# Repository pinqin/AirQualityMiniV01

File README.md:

# AirQualityMiniV01

This repository contains the design files for a printed circuit board (PCB) featuring an ESP32-C3 microcontroller and a BME688 environmental sensor.
Included are schematics, PCB layout files, and the bill of materials (BOM).
Key Components (BOM excerpt)

U1: BME688 (environmental sensor)

U2: ESP32-C3 (WiFi/Bluetooth SoC)

U3: USB-C connector – DX07S016JA1R1500

U4: Antenna – ANT3216LL00R2400A

U5: Voltage regulator – TLV62568DBVR

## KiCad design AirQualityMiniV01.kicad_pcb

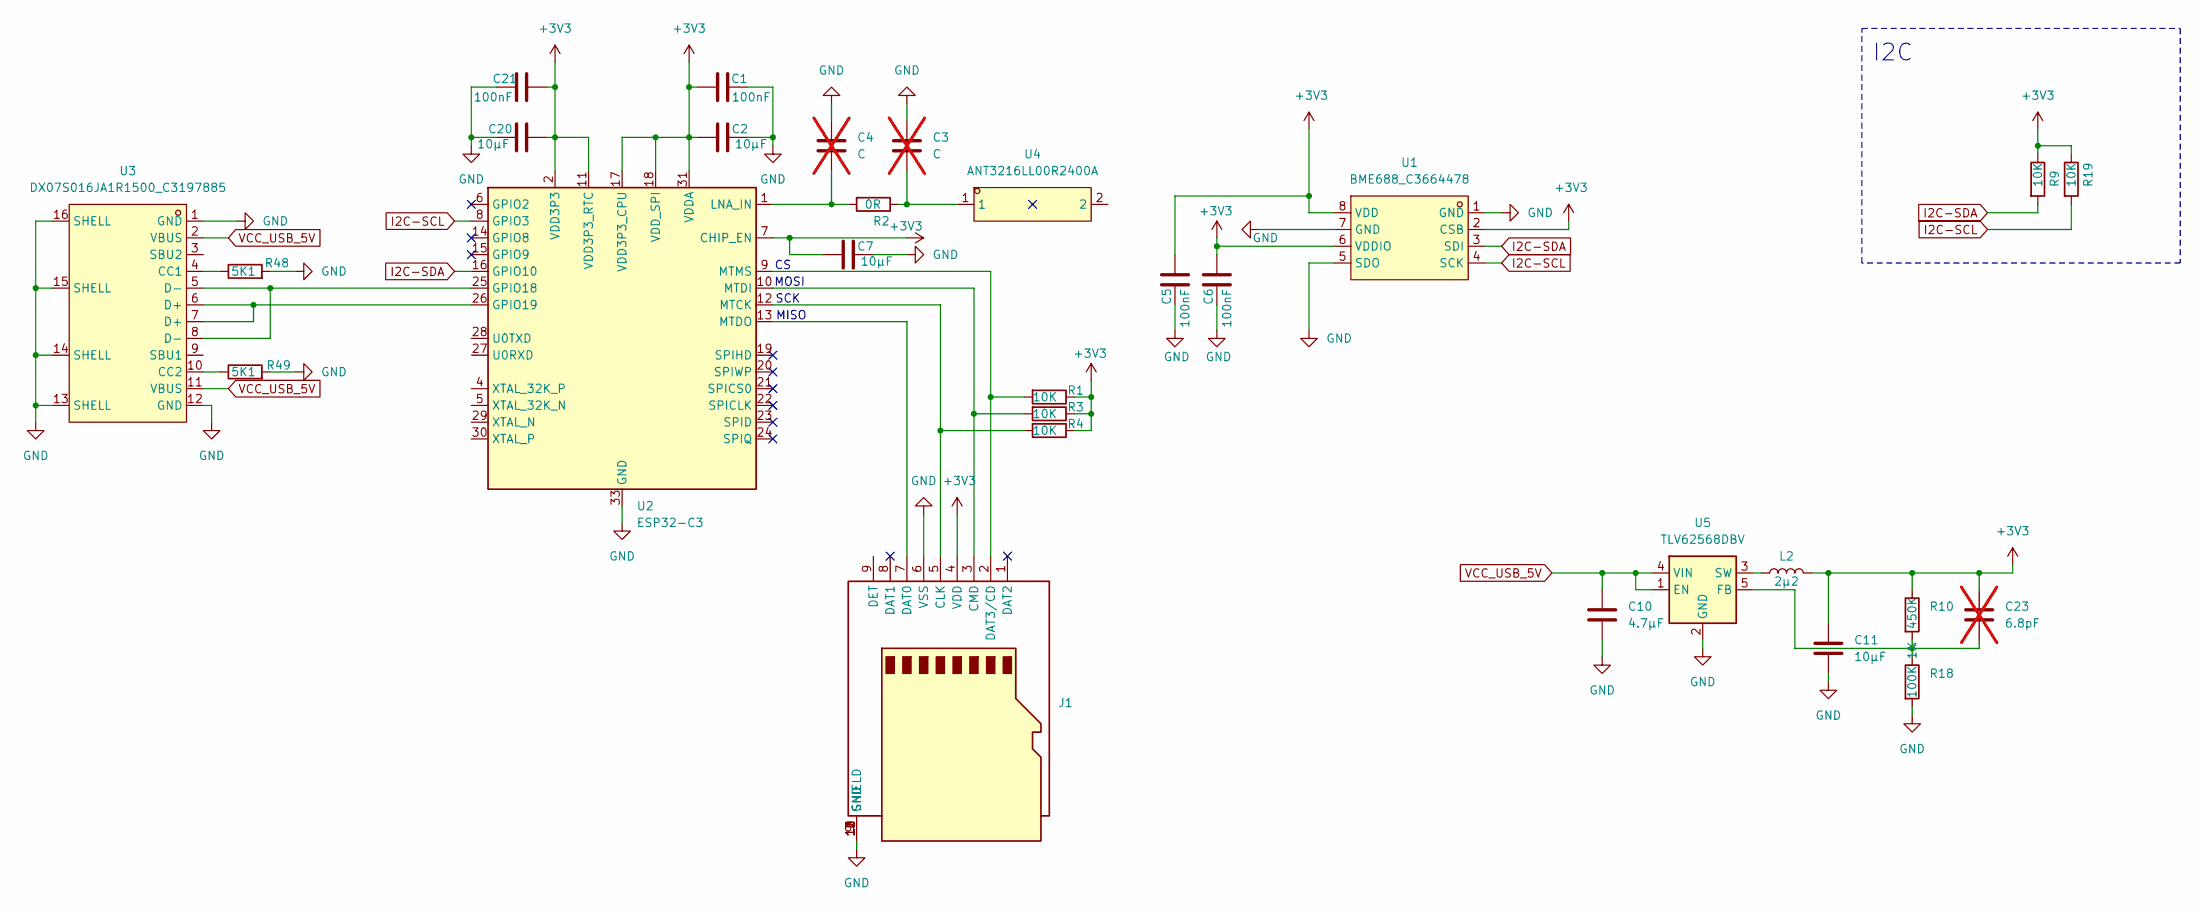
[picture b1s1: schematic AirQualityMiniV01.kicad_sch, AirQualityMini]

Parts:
C1, C5, C6, C21: 100nF; C_0603_1608Metric; MPN CC0603KRX7R9BB104; LCSC Partnumber C14663
C2, C7, C20: 10µF; C_0603_1608Metric; MPN GRM188R61A106KE69D; LCSC Partnumber C77044
C3, C4: C; C_0603_1608Metric; not fitted
C10: 4.7µF; C_0805_2012Metric; MPN GRM21BR71A475KA73L; LCSC Partnumber C86039
C11: 10µF; C_0805_2012Metric; MPN GRM21BR71A106KE51L; LCSC Partnumber C86038
C23: 6.8pF; C_0603_1608Metric; MPN CC0402CRNPO9BN6R8; LCSC Partnumber C189470; not fitted
J1: 1051620001; MPN 1051620001; LCSC Partnumber C3177046
L2: 2µ2; L_1008_2520Metric; MPN WIP252010P-2R2ML; LCSC C315713
R1, R3, R4, R9, R19: 10K; R_0603_1608Metric; MPN RC0603FR-0710KL; LCSC Partnumber C98220
R2: 0R; R_0603_1608Metric; MPN RC0603JR-070RL; LCSC Partnumber C95177
R10: 450K; R_0402_1005Metric; MPN FRC0402F4503TS; LCSC Partnumber C5159688
R18: 100K 1%; R_0603_1608Metric; MPN RC0603FR-07100KL; LCSC Partnumber C14675
R48, R49: 5K1; R_0603_1608Metric; MPN RC0603FR-075K1L; LCSC Partnumber C105580
U1: BME688_C3664478; LGA-8_L3.0-W3.0-P0.80_BME688; MPN BME688; LCSC Part C3664478
U2: ESP32-C3; QFN-32-1EP_5x5mm_P0.5mm_EP3.7x3.7mm; MPN ESP32-C3
U3: DX07S016JA1R1500_C3197885; USB-C-SMD_DX07S016JA1R1500; LCSC Part C3197885
U4: ANT3216LL00R2400A; ANT-SMD_L3.2-W1.6; MPN ANT3216LL00R2400A; LCSC Part C293767
U5: TLV62568DBV; SOT-23-5; MPN TLV62568DBVR; LCSC Partnumber C163219

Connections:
+3V3: C1.2, C2.2, C5.2, C6.2, C7.2, C11.1, C20.2, C21.2, C23.1, J1.4 (VDD), L2.2, R1.1, R3.1, R4.1, R9.1, R10.1, R19.1, U1.2 (CSB), U1.6 (VDDIO), U1.8 (VDD), U2.2 (VDD3P3), U2.3 (VDD3P3), U2.7 (CHIP_EN), U2.11 (VDD3P3_RTC), U2.17 (VDD3P3_CPU), U2.18 (VDD_SPI), U2.31 (VDDA), U2.32 (VDDA)
GND: C1.1, C2.1, C3.1, C4.1, C5.1, C6.1, C7.1, C10.2, C11.2, C20.1, C21.1, J1.6 (VSS), J1.9 (SHIELD), J1.10 (GND), J1.11 (GND), J1.12 (GND), J1.13 (GND), R18.2, R48.2, R49.2, U1.1 (GND), U1.5 (SDO), U1.7 (GND), U2.33 (GND), U3.1 (GND), U3.12 (GND), U3.13 (SHELL), U3.14 (SHELL), U3.15 (SHELL), U3.16 (SHELL), U5.2 (GND)
I2C-SCL: R19.2, U1.4 (SCK), U2.8 (GPIO3)
I2C-SDA: R9.2, U1.3 (SDI), U2.16 (GPIO10)
unnamed: C3.2, R2.1, U4.1
unnamed: J1.5 (CLK), R4.2, U2.12 (MTCK)
unnamed: J1.3 (CMD), R3.2, U2.10 (MTDI)
unnamed: J1.7 (DAT0), U2.13 (MTDO)
unnamed: J1.2 (DAT3/CD), R1.2, U2.9 (MTMS)
unnamed: U2.25 (GPIO18), U3.5 (D-), U3.8 (D-)
unnamed: U2.26 (GPIO19), U3.6 (D+), U3.7 (D+)
unnamed: C4.2, R2.2, U2.1 (LNA_IN)
unnamed: R48.1, U3.4 (CC1)
unnamed: R49.1, U3.10 (CC2)
unnamed: C23.2, R10.2, R18.1, U5.5 (FB)
unnamed: L2.1, U5.3 (SW)
VCC_USB_5V: C10.1, U3.2 (VBUS), U3.11 (VBUS), U5.1 (EN), U5.4 (VIN)

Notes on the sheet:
MOSI
MISO
SCK
I2C

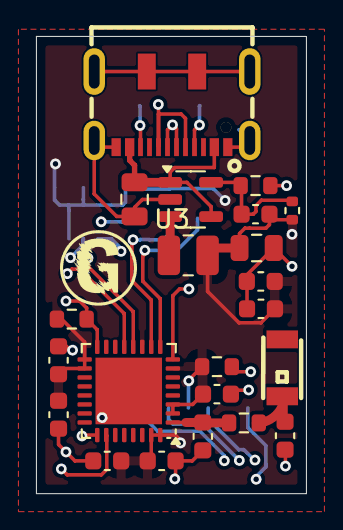
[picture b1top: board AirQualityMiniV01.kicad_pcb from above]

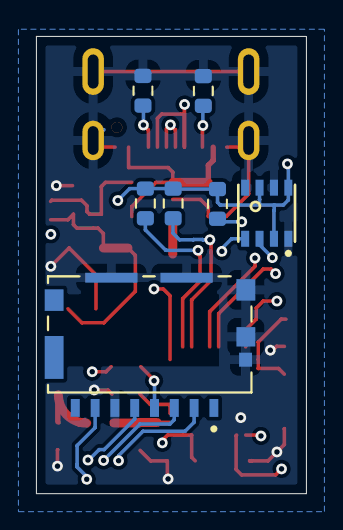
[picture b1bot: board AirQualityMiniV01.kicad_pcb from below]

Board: 4 copper layers, 15.0 x 25.4 mm, 29 parts (7 on the bottom side), 17 nets.

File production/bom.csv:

Designator,Footprint,Quantity,Value,LCSC Part #
"C1, C21, C5, C6",0603,4,100nF,CC0603KRX7R9BB104
C10,0805,1,4.7µF,GRM21BR71A475KA73L
C11,0805,1,10µF,GRM21BR71A106KE51L
"C2, C20, C7",0603,3,10µF,GRM188R61A106KE69D
C23,0603,1,6.8pF,CC0402CRNPO9BN6R8
"C3, C4",0603,2,C,
J1,1051620001,1,~,1051620001
L2,1008,1,2µ2,C315713
"R1, R19, R3, R4, R9",0603,5,10K,RC0603FR-0710KL
R10,0402,1,450K,FRC0402F4503TS
R18,0603,1,100K 1%,RC0603FR-07100KL
R2,0603,1,0R,RC0603JR-070RL
"R48, R49",0603,2,5K1,RC0603FR-075K1L
U1,LGA-8_L3.0-W3.0-P0.80_BME688,1,BME688_C3664478,C3664478
U2,QFN-32-1EP_5x5mm_P0.5mm_EP3.7x3.7mm,1,ESP32-C3,ESP32-C3
U3,USB-C-SMD_DX07S016JA1R1500,1,DX07S016JA1R1500_C3197885,C3197885
U4,ANT-SMD_L3.2-W1.6,1,ANT3216LL00R2400A,C293767
U5,SOT-23-5,1,TLV62568DBV,TLV62568DBVR
